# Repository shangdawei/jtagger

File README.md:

# jtagger?

Well, it's not really just a jtagger, but I've been calling it that. It's also
been christened the Bit Quacker... uh, because it quacks? \*shrug\*

The basis for this design is sort of like the [Bus Blaster](http://dangerousprototypes.com/docs/Bus_Blaster), with a few nice mods. It's smaller (I'm working on V2, which may or may not ever be finished, which will be even smaller), it has an FPGA instead of a CPLD (not only more versatile, but will never be worn out by writes and rewrites), it's 5V-capable, and it can even do up to 13V on one pin, to enable programming microcontrollers with HVP.

The idea is that this can be adapted to program (as close to literally as possible) _any_ serial-programmed logic device, and debugging can be done as well.

In its most basic form, it's compatible with FT2232-compatible JTAG tools, as a simple firmware can be loaded to the FPGA that just passes the [MPSSE](http://www.ftdichip.com/Support/Documents/AppNotes/AN_135_MPSSE_Basics.pdf) signals straight through. The second port on the FT2232 can program the FPGA, so it's self-programming (it does, however, have a flash memory, so it can be preloaded with a firmware to skip this step).

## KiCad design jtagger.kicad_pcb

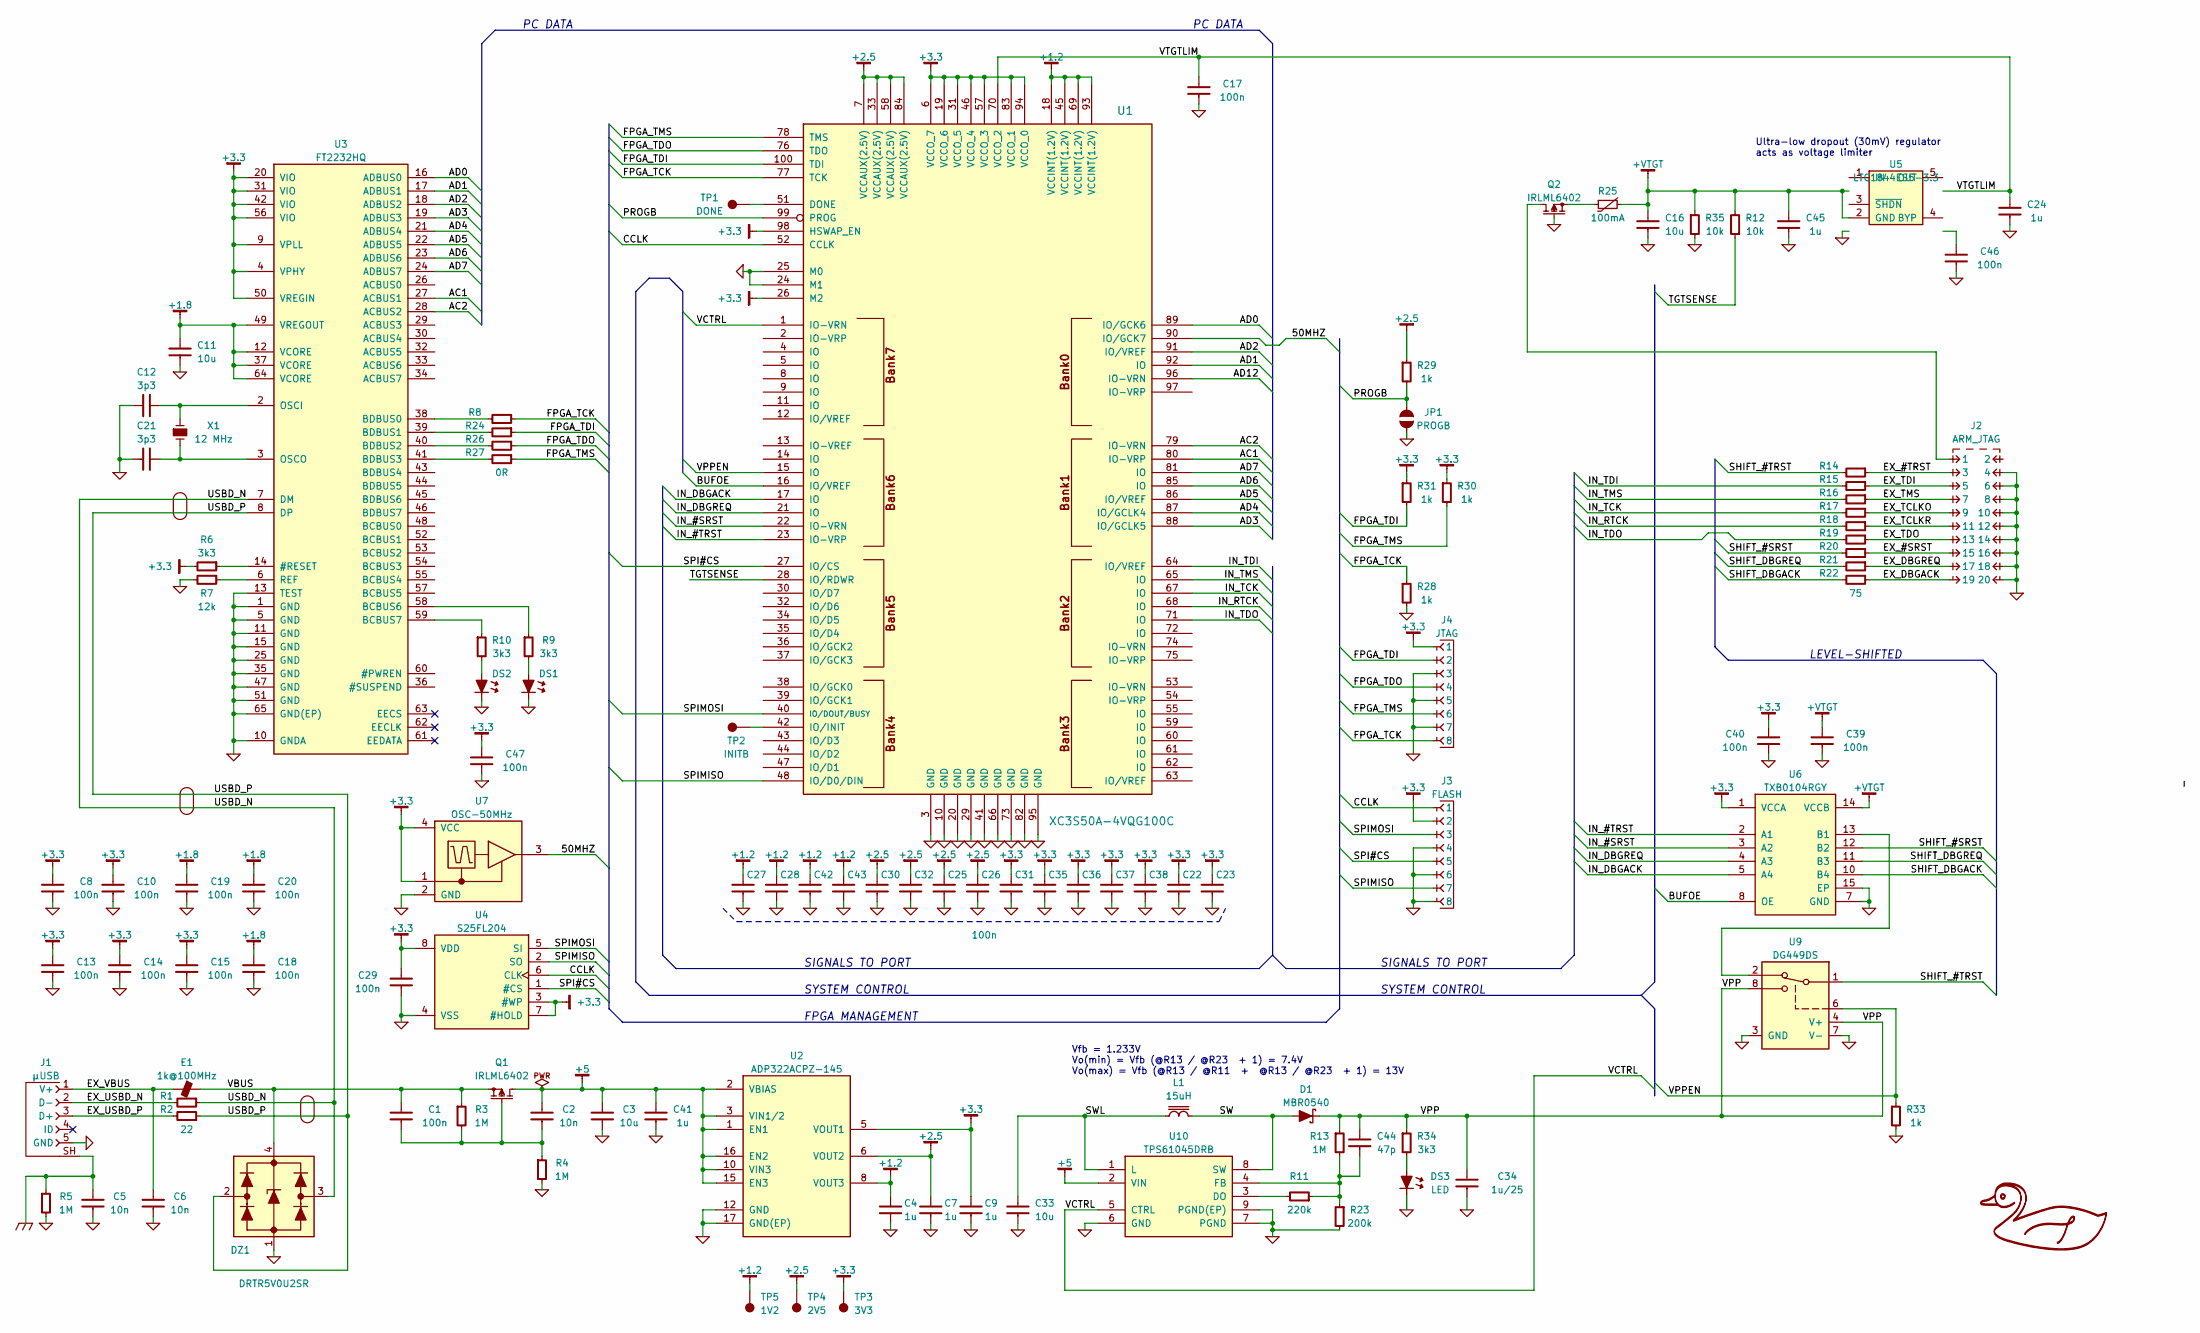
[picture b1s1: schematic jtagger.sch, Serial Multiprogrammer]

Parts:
C1, C8, C10, C13, C14, C15, C17, C18, C19, C20, C22, C23, C25, C26, C27, C28, C29, C30, C31, C32, C35, C36, C37, C38, C39, C40, C42, C43, C46, C47: 100n; CAPC1005X55
C2, C5, C6: 10n; CAPC1005X55
C3, C11, C16, C33: 10u; CAPC2012X70
C4, C7, C9, C24, C41, C45: 1u; CAPC1608X55
C12, C21: 3p3; CAPC1005X55
C34: 1u/25; CAPC3216X70
C44: 47p; CAPC1005X55
D1: MBR0540; SOD-123
DS1, DS2: LED-0603
DS3: LED; LED-0603
DZ1: DRTR5V0U2SR; SOT-143
E1: 1k@100MHz; INDC1608X95
J1: µUSB; CONN-10118194-0001LF-FCI
J2: ARM_JTAG; CONN-100MIL-M-2x10-SHROUD
J3: FLASH; CONN-MOLEX-52808-0871
J4: JTAG; CONN-MOLEX-52808-0871
JP1: PROGB
L1: 15uH; BOURNS-SRN3015
Q1, Q2: IRLML6402; SOT-23
R1, R2: 22; RESC1005X40
R3, R4, R5, R13: 1M; RESC1005X40
R6, R9, R10, R34: 3k3; RESC1005X40
R7: 12k; RESC1005X40
R8, R24, R26, R27: 0R; RESC1005X40
R11: 220k; RESC1005X40
R12, R35: 10k; RESC1005X40
R14, R15, R16, R17, R18, R19, R20, R21, R22: 75; RESC2012X50
R23: 200k; RESC1005X40
R25: 100mA; RESC2012X50
R28, R29, R30, R31, R33: 1k; RESC1005X40
TP1: DONE; TEST-SMD-SMALL
TP2: INITB; TEST-SMD-SMALL
TP3: 3V3; TEST-SMD-SMALL
TP4: 2V5; TEST-SMD-SMALL
TP5: 1V2; TEST-SMD-SMALL
U1: XC3S50A-4VQG100C; QFP50P1600X1600X100-100
U2: ADP322ACPZ-145; QFN50P300X300X100-17
U3: FT2232HQ; QFN50P900X900X100-65
U4: S25FL204; SOIC127P600X175-8
U5: LTC1844ES5-3.3; SOT-23-5
U6: TXB0104RGY; TEXAS-RGY
U7: OSC-50MHz; SILABS-DFN-SI501-B
U9: DG449DS; SOT-23-8
U10: TPS61045DRB; SON65P300X300X80-9
X1: 12 MHz; XTAL1200X480X460

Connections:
+1.2: C4.1, C27.1, C28.1, C42.1, C43.1, TP5.1, U1.18 (VCCINT(1.2V)), U1.45 (VCCINT(1.2V)), U1.69 (VCCINT(1.2V)), U1.93 (VCCINT(1.2V)), U2.8 (VOUT3)
+1.8: C11.1, C18.1, C19.1, C20.1, U3.12 (VCORE), U3.37 (VCORE), U3.49 (VREGOUT), U3.64 (VCORE)
+2.5: C7.1, C25.1, C26.1, C30.1, C32.1, R29.1, TP4.1, U1.7 (VCCAUX(2.5V)), U1.33 (VCCAUX(2.5V)), U1.58 (VCCAUX(2.5V)), U1.84 (VCCAUX(2.5V)), U2.6 (VOUT2)
+3.3: C8.1, C9.1, C10.1, C13.1, C14.1, C15.1, C22.1, C23.1, C29.1, C31.1, C35.1, C36.1, C37.1, C38.1, C40.1, C47.1, J3.2, J4.1, R6.2, R30.1, R31.1, TP3.1, U1.6 (VCCO_7), U1.19 (VCCO_6), U1.26 (M2), U1.31 (VCCO_5), U1.46 (VCCO_4), U1.57 (VCCO_3), U1.83 (VCCO_1), U1.94 (VCCO_0), U1.98 (HSWAP_EN), U2.5 (VOUT1), U3.4 (VPHY), U3.9 (VPLL), U3.20 (VIO), U3.31 (VIO), U3.42 (VIO), U3.50 (VREGIN), U3.56 (VIO), U4.3 (#WP), U4.7 (#HOLD), U4.8 (VDD), U6.1 (VCCA), U7.1 (OE), U7.4 (VCC)
+5: C2.1, C3.1, C41.1, Q1.3, U2.1 (EN1), U2.2 (VBIAS), U2.3 (VIN1/2), U2.10 (VIN3), U2.15 (EN3), U2.16 (EN2), U10.2 (VIN)
/50MHZ: U1.90 (IO/GCK7), U7.3 (OUT)
/AD0: U1.89 (IO/GCK6), U3.16 (ADBUS0)
/AD1: U1.92 (IO), U3.17 (ADBUS1)
/AD2: U1.91 (IO/VREF), U3.18 (ADBUS2)
/AD3: U1.88 (IO/GCLK5), U3.19 (ADBUS3)
/AD4: U1.87 (IO/GCLK4), U3.21 (ADBUS4)
/AD5: U1.86 (IO/VREF), U3.22 (ADBUS5)
/AD6: U1.85 (IO), U3.23 (ADBUS6)
/AD7: U1.81 (IO), U3.24 (ADBUS7)
/AD8: U3.26 (ACBUS0)
/AD9: U1.80 (IO-VRP), U3.27 (ACBUS1)
/AD10: U1.79 (IO-VRN), U3.28 (ACBUS2)
/AD11: U3.29 (ACBUS3)
/AD12: U1.96 (IO-VRN), U3.30 (ACBUS4)
/AD13: U3.32 (ACBUS5)
/AD14: U3.33 (ACBUS6)
/AD15: U3.34 (ACBUS7)
/BUFOE: U1.16 (IO/VREF), U6.8 (OE)
/CCLK: J3.1, U1.52 (CCLK), U4.6 (CLK)
/DONE: TP1.1, U1.51 (DONE)
/EX_#SRST: J2.15, R20.1
/EX_#TRST: J2.3, R14.1
/EX_DBGACK: J2.19, R22.1
/EX_DBGREQ: J2.17, R21.1
/EX_TCLKO: J2.9, R17.1
/EX_TCLKR: J2.11, R18.1
/EX_TDI: J2.5, R15.1
/EX_TDO: J2.13, R19.1
/EX_TMS: J2.7, R16.1
/EX_USBD_N: J1.2 (D-), R1.2
/EX_USBD_P: J1.3 (D+), R2.2
/EX_VBUS: C6.1, E1.1, J1.1 (V+)
/FPGA_TCK: J4.8, R8.1, R28.1, U1.77 (TCK)
/FPGA_TDI: J4.2, R24.1, R31.2, U1.100 (TDI)
/FPGA_TDO: J4.4, R26.1, U1.76 (TDO)
/FPGA_TMS: J4.6, R27.1, R30.2, U1.78 (TMS)
/IN_#SRST: U1.22 (IO-VRN), U6.3 (A2)
/IN_#TRST: U1.23 (IO-VRP), U6.2 (A1)
/IN_DBGACK: U1.17 (IO), U6.5 (A4)
/IN_DBGREQ: U1.21 (IO), U6.4 (A3)
/IN_RTCK: R18.2, U1.68 (IO)
/IN_TCK: R17.2, U1.67 (IO)
/IN_TDI: R15.2, U1.64 (IO/VREF)
/IN_TDO: R19.2, U1.71 (IO)
/IN_TMS: R16.2, U1.65 (IO)
/SPI#CS: J3.5, U1.27 (IO/CS), U4.1 (#CS)
/SPIMISO: J3.7, U1.48 (IO/D0/DIN), U4.2 (SO)
/SPIMOSI: J3.3, U1.40 (IO/DOUT/BUSY), U4.5 (SI)
/SW: D1.2, L1.1, U10.8 (SW)
/SWL: C33.1, L1.2, U10.1 (L)
/TGTSENSE: R12.1, U1.28 (IO/RDWR)
/USBD_N: DZ1.3, R1.1, U3.7 (DM)
/USBD_P: DZ1.2, R2.1, U3.8 (DP)
/VBUS: C1.1, DZ1.4, E1.2, Q1.2, R3.1
/VCTRL: U1.1 (IO-VRN), U10.5 (CTRL)
/VPP: C34.1, C44.1, D1.1, R13.1, R34.1, U9.4 (V+), U9.8
/VPPEN: R33.1, U1.15 (IO), U9.6
/VTGTLIM: C17.1, C24.1, U1.70 (VCCO_2), U5.5 (OUT)
CGND: C5.1, J1.SH (SHIELD), R5.1
unnamed: C1.2, C2.2, Q1.1, R3.2, R4.1
unnamed: C12.1, U3.2 (OSCI), X1.1
unnamed: C21.1, U3.3 (OSCO), X1.2
unnamed: C44.2, R11.1, R13.2, R23.1, U10.4 (FB)
unnamed: C46.1, U5.4 (BYP)
unnamed: DS1.2, R9.2
unnamed: DS2.2, R10.2
unnamed: DS3.2, R34.2
unnamed: J2.1, Q2.3
unnamed: JP1.1, R29.2, U1.99 (PROG)
unnamed: Q2.2, R25.1
unnamed: R6.1, U3.14 (#RESET)
unnamed: R7.1, U3.6 (REF)
unnamed: R8.2, U3.38 (BDBUS0)
unnamed: R9.1, U3.58 (BCBUS6)
unnamed: R10.1, U3.59 (BCBUS7)
unnamed: R11.2, U10.3 (DO)
unnamed: R14.2, U9.1
unnamed: R20.2, U6.12 (B2)
unnamed: R21.2, U6.11 (B3)
unnamed: R22.2, U6.10 (B4)
unnamed: R24.2, U3.39 (BDBUS1)
unnamed: R26.2, U3.40 (BDBUS2)
unnamed: R27.2, U3.41 (BDBUS3)
unnamed: TP2.1, U1.42 (IO/INIT)
unnamed: U6.13 (B1), U9.2

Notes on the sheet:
Vfb = 1.233V Vo(min) = Vfb (@R13 / @R23 + 1) = 7.4V Vo(max) = Vfb (@R13 / @R11 + @R13 / @R23 + 1) = 13V
SIGNALS TO PORT
SYSTEM CONTROL
FPGA MANAGEMENT
PC DATA
LEVEL-SHIFTED
Ultra-low dropout (30mV) regulator acts as voltage limiter

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
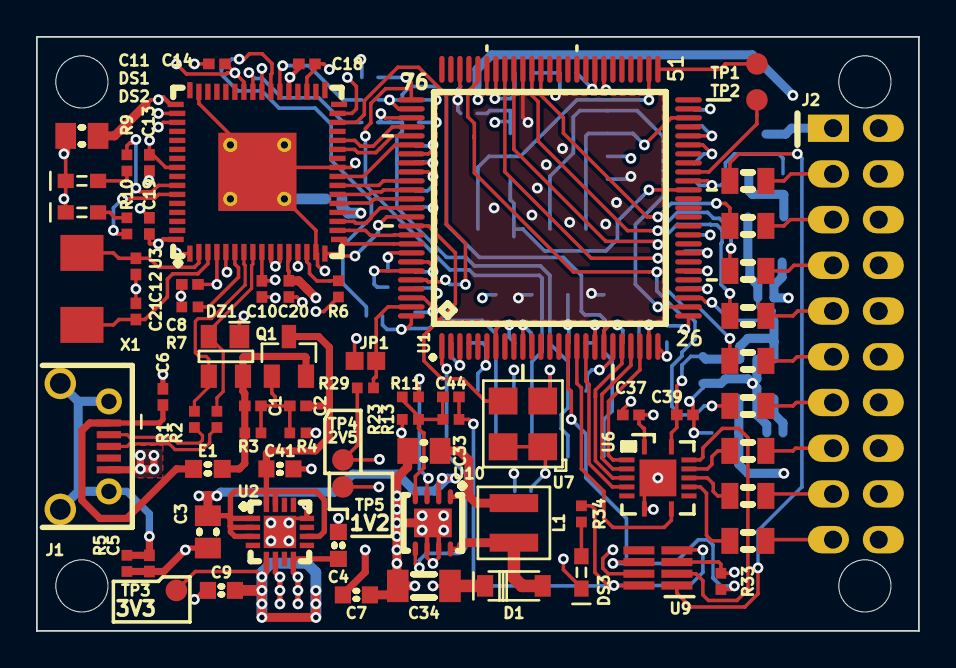
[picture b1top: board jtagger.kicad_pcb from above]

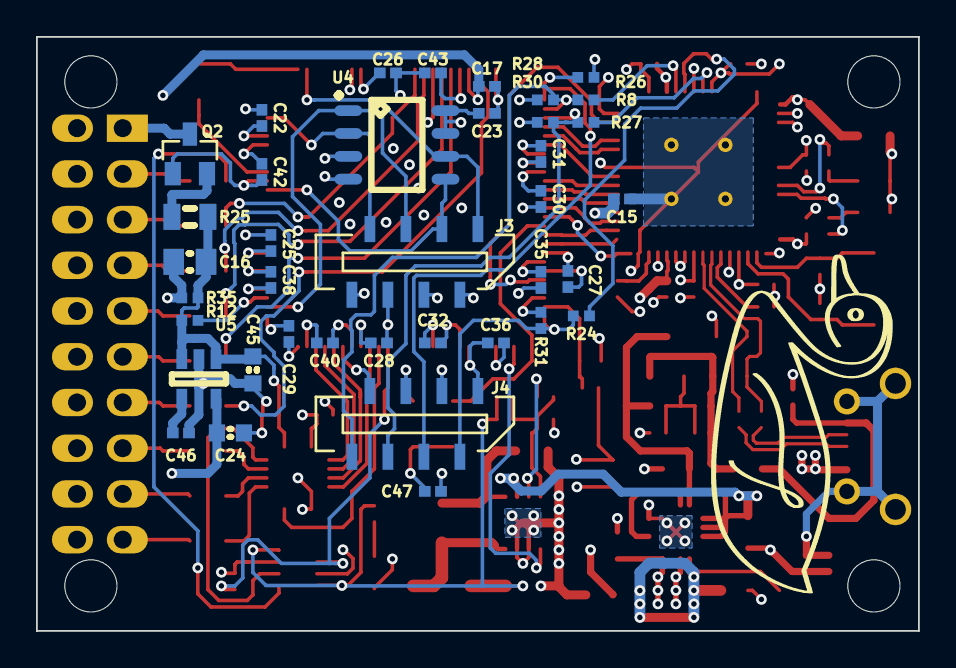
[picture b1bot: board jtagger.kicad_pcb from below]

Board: 4 copper layers, 49.0 x 33.0 mm, 110 parts (38 on the bottom side), 87 nets.

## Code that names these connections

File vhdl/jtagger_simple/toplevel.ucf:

NET "bufoe" LOC = P16;
NET "clk" LOC = P90;

# PlanAhead Generated physical constraints

NET "ftdi_ac1" LOC = P80;
NET "ftdi_ac2" LOC = P79;
NET "ftdi_ad0" LOC = P89;
NET "ftdi_ad1" LOC = P92;
NET "ftdi_ad2" LOC = P91;
NET "ftdi_ad3" LOC = P88;
NET "ftdi_ad4" LOC = P87;
NET "ftdi_ad5" LOC = P86;
NET "ftdi_ad6" LOC = P85;
NET "ftdi_ad7" LOC = P81;
NET "iopin_3" LOC = P23;
NET "iopin_5" LOC = P64;
NET "iopin_7" LOC = P65;
NET "iopin_9" LOC = P67;
NET "iopin_11" LOC = P68;
NET "iopin_13" LOC = P71;
NET "iopin_15" LOC = P22;
NET "iopin_17" LOC = P21;
NET "iopin_19" LOC = P17;
NET "tgtsense" LOC = P28;
NET "vctrl" LOC = P1;
NET "vppen" LOC = P15;

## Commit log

2015-04-09 Checkin
2015-04-09 Version submitted to fab
2015-04-10 Schematic stuff
2015-04-21 Fix PCB bug: FT2232 thermal pad too big
2015-04-21 Remove old VHDL
2015-04-23 Add "simple" VHDL
2015-04-23 Added README, LICENSE
2015-04-23 Add ISE Makefile
2015-04-23 Cleanup ISE files
2015-04-24 Tweak Makefile, add 'make program'
